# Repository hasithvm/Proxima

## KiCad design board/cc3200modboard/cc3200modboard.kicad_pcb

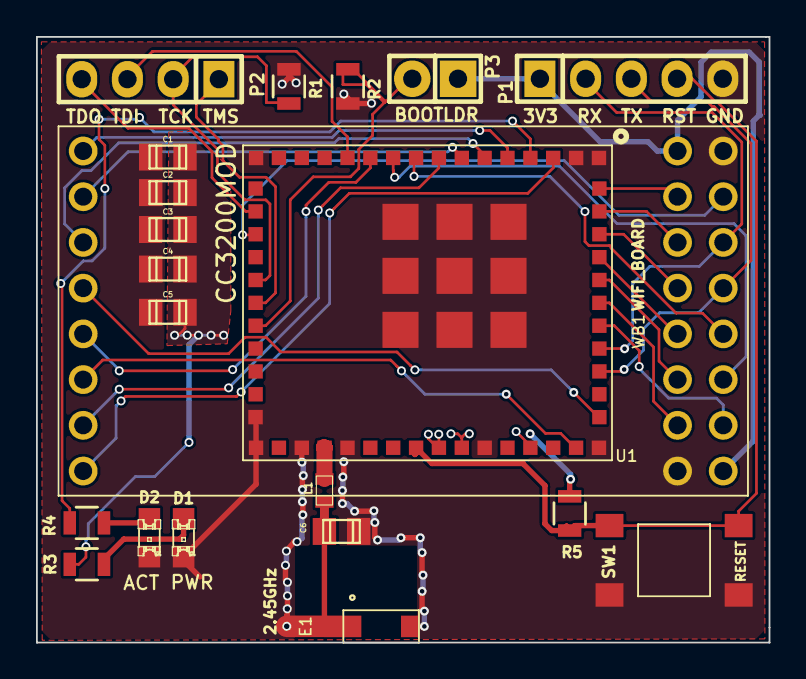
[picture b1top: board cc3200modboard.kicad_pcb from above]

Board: 2 copper layers, 40.7 x 33.6 mm, 21 parts (0 on the bottom side), 33 nets.

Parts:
C1, C2, C3, C4, C5: 22uF; c_0805
C6: 1.0pF; c_0805
D1: PWR; LED-0805
D2: ACT; LED-0805
E1: 2.45GHz; 2.4GHz_ANT_AH316M245001-T
L1: 3.6nH; IND_RF_0603
P1: PROG; Pin_Header_Straight_1x05
P2: JTAG; Pin_Header_Straight_1x04
P3: BOOTLDR; Pin_Header_Straight_1x02
R1: 100K; R_0805
R2: 2.7K; R_0805
R3, R4: 560; R_0805
R5: 10K; R_0805
SW1: RESET; PTS645
U1: CC3200MOD
WB1: WIFI_BOARD; DaughterBoard

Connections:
3V3: C1.1, C2.1, C3.1, C4.1, C5.1, P1.1, P3.1, R3.1, R5.1, U1.36, U1.37, U1.40, WB1.9, WB1.17
/GPIO0: U1.44, WB1.4
/GPIO1: P1.3, U1.46, WB1.13
/GPIO2: P1.2, U1.47, WB1.14
/GPIO3: U1.48, WB1.10
/GPIO4: U1.49, WB1.23
/GPIO5: U1.50, WB1.22
/GPIO6: U1.51, WB1.21
/GPIO7: U1.52, WB1.20
/GPIO8: U1.53, WB1.19
/GPIO9: U1.54, WB1.18
/GPIO10: U1.3, WB1.8
/GPIO11: R4.1, U1.4
/GPIO12: U1.9, WB1.12
/GPIO13: U1.10, WB1.11
/GPIO14: U1.5, WB1.1
/GPIO15: U1.6, WB1.3
/GPIO16: U1.7, WB1.2
/GPIO17: U1.8, WB1.7
/GPIO22: U1.11, WB1.5
/GPIO28: U1.19, WB1.15
/GPIO30: U1.42, WB1.6
/IMP_50OHM: L1.1, U1.31
/RF_FEED: C6.1, E1.1, L1.2
/SOP2: P3.2, R2.1, U1.23
/TCK: P2.2, R1.1, U1.21
/TDI: P2.3, U1.12
/TDO: P2.4, U1.18
/TMS: P2.1, U1.22
/nRESET: P1.4, R5.2, SW1.2, U1.35
GND: C1.2, C2.2, C3.2, C4.2, C5.2, C6.2, D1.2, D2.2, E1.2, P1.5, R1.2, R2.2, SW1.1, U1.1, U1.2, U1.16, U1.27, U1.28, U1.30, U1.32, U1.38, U1.43, U1.55, U1.56, U1.57, U1.58, U1.59, U1.60, U1.61, U1.62, U1.63, WB1.16, WB1.24
unnamed: D1.1, R3.2
unnamed: D2.1, R4.2

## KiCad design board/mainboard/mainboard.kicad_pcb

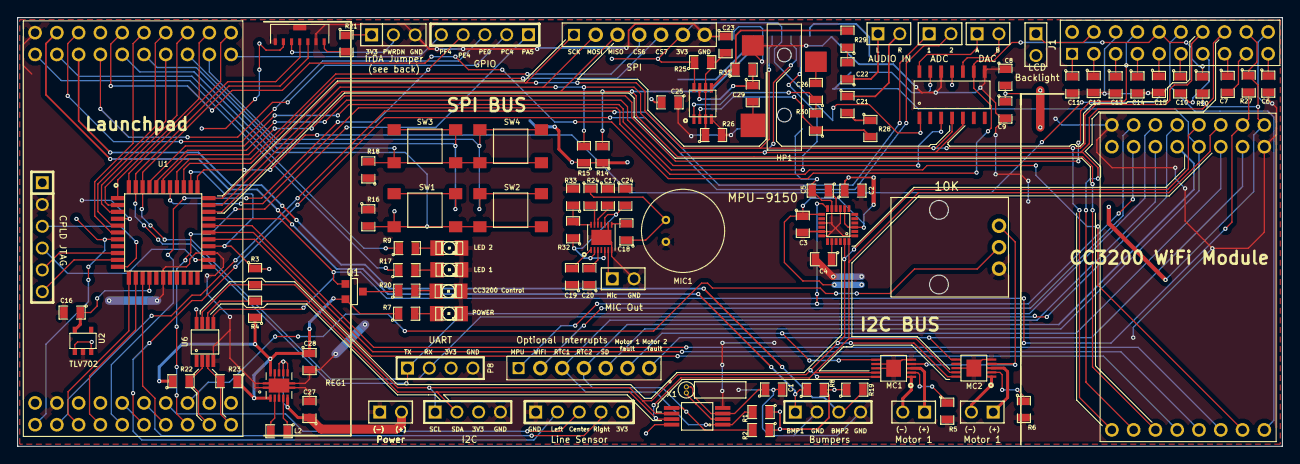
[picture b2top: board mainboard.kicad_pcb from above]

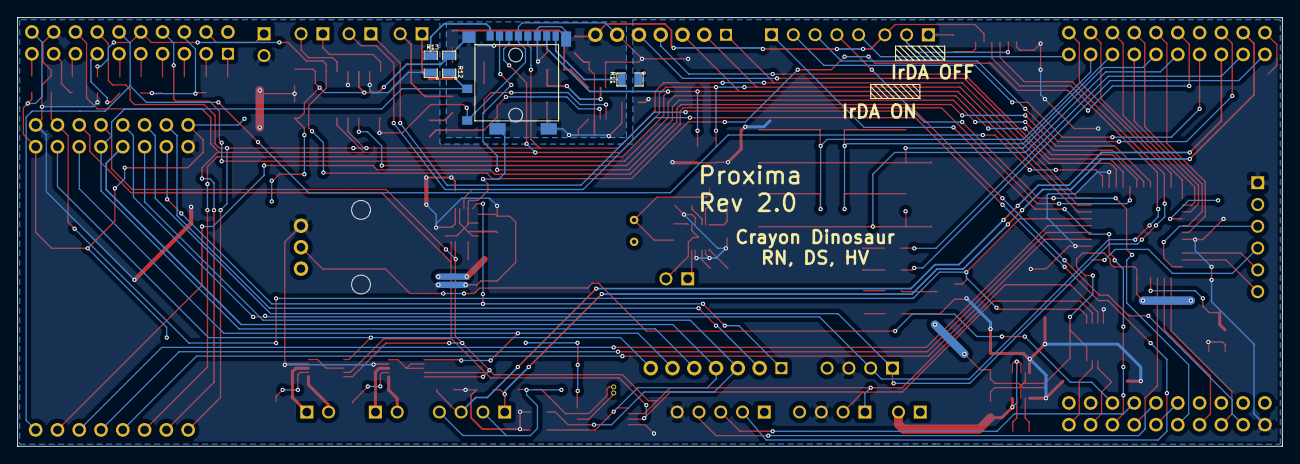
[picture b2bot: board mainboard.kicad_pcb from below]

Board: 2 copper layers, 147.5 x 50.0 mm, 109 parts (4 on the bottom side), 117 nets.

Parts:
AUD1: LM4808
C1: 5pF; SM0805
C2, C5, C8, C24: 0.1uF; SM0805
C3: 10nF; SM0805
C4: 2.2nF; SM0805
C6, C7, C10, C11, C12, C13, C14, C15, C16, C25: 1uF; SM0805
C9, C27, C28: 10uF; SM0805
C17: 470nF; SM0805
C18, C19: 680nF; SM0805
C20, C21, C22: 2.2uF; SM0805
C23: 1.0uF; SM0805
C26, C29: 100uF; SM0805
D1: GLED; LED-1206
D2: RLED; LED-1206
D3: POWER; LED-1206
D4: CONTROL; LED-1206
DAC1: MCP4902
GLCD1: NHD-C12832A1Z-NSW-BBW-3V3; 2x10_Headers
HP1: HP_JACK; HeadphoneJack
IR1: RPM841-H11; RPM973-H11
J1: BACKL; PIN_ARRAY_2X1
K1: IRDA_EN; PIN_ARRAY_3X1
L2: 2.2uH; SM0805
LP1: TIVALAUNCHPAD; TivaC
MC1, MC2: DRV8830; DRV8830MSOP
MIC1: CMA-4544PF-W; CMA-4544
MPU1: MPU-9150; MPU9150
P1: I2C; PIN_ARRAY_4x1
P2: Motor1; PIN_ARRAY_2X1
P3: Motor2; PIN_ARRAY_2X1
P4: SPI; 1x7_Headers
P5: DAC; PIN_ARRAY_2X1
P6: CONN_5; PIN_ARRAY_5x1
P7: ANALOG; PIN_ARRAY_2X1
P8: OPTIONAL_PERIPH; 1x7_Headers
P9: GPIO; PIN_ARRAY_5x1
P10: BUMPERS; PIN_ARRAY_4x1
P11: CPLD_JTAG; PIN_ARRAY-6X1
P12: POWER; PIN_ARRAY_2X1
P13: UART; PIN_ARRAY_4x1
P14: AUDIO; PIN_ARRAY_2X1
P15: MIC; PIN_ARRAY_2X1
Q1: BSS84; SOT23GDS
R1, R2, R16, R18, R27: 10K; SM0805
R3, R4, R22, R23: 4.7k; SM0805
R5, R6: 0.2; SM0805
R7, R9, R17, R20: 220; SM0805
R8, R11, R13, R14, R15, R19: 47k; SM0805
R10, R12: 10k; SM0805
R21: 3; SM0805
R24: 2.2k; SM0805
R25, R26: 100k; SM0805
R28, R29, R30, R31: 3.9k; SM0805
R32, R33: 150k; SM0805
REG1: TPS63001
RTC1: S-35390A; S35390A
RV1: 10K; P090_Potentiometer
SD1: SDCARD_PUSH; SDCARD_Push
SW1, SW2, SW3, SW4: SW_PUSH; PTS645
U1: XC2C32A; CoolrunnerII
U2: TLV702; SOT23-5
U3: MAX9814
U6: PCA9515B
WB1: WIFI_BOARD; DaughterBoard
X1: 32.768KHz; XTAL-32K

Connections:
3V3: AUD1.8, C2.1, C3.1, C8.2, C9.1, C24.2, C25.2, C28.1, DAC1.1, DAC1.11, DAC1.13, GLCD1.12, IR1.6, J1.2, K1.1, LP1.1, MC1.4, MC2.4, MPU1.3, MPU1.8, MPU1.13, P1.3, P4.6, P6.5, P11.1, P13.3, Q1.S, R1.1, R2.1, R3.1, R4.1, R7.1, R8.2, R10.2, R11.1, R13.1, R14.1, R15.1, R19.1, R21.1, R22.1, R23.1, R25.1, R27.1, R32.1, REG1.1, REG1.10, RTC1.8, RV1.3, SD1.4, SD1.9, U1.7, U1.26, U1.35, U2.1, U2.3, U3.2, U3.5, U3.10, U6.8, WB1.9, WB1.17
+1.8V: C16.1, U1.15, U2.5
AIN1: LP1.2, P7.1
AIN2: LP1.6, P7.2
BUMP1: LP1.19, P10.1, R8.1
BUMP2: LP1.38, P10.3, R19.2
CC_CONTROL: Q1.G, R27.2, U1.30, U6.5, WB1.10
CPLD_TCK: P11.3, U1.11
CPLD_TDI: P11.5, U1.9
CPLD_TDO: P11.4, U1.24
CPLD_TMS: P11.6, U1.10
GLCD_A0: GLCD1.15, U1.34, WB1.8
GLCD_A0_LP: LP1.34, U1.3
GND: AUD1.4, C1.2, C2.2, C3.2, C4.2, C5.2, C6.2, C8.1, C9.2, C11.2, C12.2, C13.2, C14.2, C15.2, C16.2, C17.1, C19.1, C20.1, C23.1, C24.1, C25.1, C27.2, C28.2, D1.2, D2.2, D3.2, D4.2, DAC1.8, DAC1.12, GLCD1.11, GLCD1.18, HP1.5, IR1.2, IR1.7, K1.3, LP1.20, LP1.22, MC1.5, MC1.7, MC1.8, MC2.5, MC2.8, MIC1.2, MPU1.1, MPU1.9, MPU1.11, MPU1.15, MPU1.17, MPU1.18, P1.4, P4.7, P6.1, P10.2, P10.4, P11.2, P12.1, P13.4, P15.2, R5.2, R6.2, R12.2, R16.1, R18.1, R26.2, R33.2, REG1.3, REG1.9, RTC1.4, RV1.1, SD1.6, U1.4, U1.17, U1.25, U2.2, U3.7, U3.9, U6.4, WB1.16, WB1.24
I2C_CL: MC1.10, MC2.10, MPU1.23, P1.1, R3.2, RTC1.6, U6.7, WB1.12
I2C_CL_LP: LP1.9, R22.2, U6.2
I2C_DA: MC1.9, MC2.9, MPU1.24, P1.2, R4.2, RTC1.7, U6.6, WB1.11
I2C_DA_LP: LP1.10, R23.2, U6.3
KPAD_C1: LP1.36, R16.2, SW1.2, SW2.2
KPAD_C2: LP1.35, R18.2, SW3.2, SW4.2
KPAD_R1: LP1.33, SW1.1, SW3.1
KPAD_R2: LP1.32, SW2.1, SW4.1
LED1: LP1.40, R17.1
LED2: LP1.39, R9.1
LINE_SENSOR_C: LP1.27, P6.3
LINE_SENSOR_L: LP1.25, P6.2
LINE_SENSOR_R: LP1.26, P6.4
MOTOR1+: MC1.3, P2.1
MOTOR1-: MC1.1, P2.2
MOTOR1F: MC1.6, P8.6, WB1.22
MOTOR2+: MC2.3, P3.1
MOTOR2-: MC2.1, P3.2
MOTOR2F: MC2.6, P8.7, WB1.23
MPUINT: MPU1.12, P8.1, WB1.18
unnamed: MC2.2, R6.1
unnamed: C5.1, MPU1.10
unnamed: C4.1, MPU1.20
unnamed: MC1.2, R5.1
unnamed: C1.1, RTC1.3, X1.1
unnamed: RTC1.2, X1.2
unnamed: DAC1.10, P5.2
unnamed: DAC1.14, P5.1
unnamed: R13.2, SD1.1
unnamed: C15.1, GLCD1.5
unnamed: C14.1, GLCD1.4
unnamed: C13.1, GLCD1.3
unnamed: C12.1, GLCD1.2
unnamed: C6.1, GLCD1.10
unnamed: C11.1, GLCD1.1
unnamed: R11.2, SD1.8
unnamed: GLCD1.19, J1.1
unnamed: C10.1, GLCD1.6
unnamed: C7.1, GLCD1.8
unnamed: C7.2, GLCD1.9
unnamed: C10.2, GLCD1.7
unnamed: D2.1, R17.2
unnamed: IR1.5, K1.2
unnamed: IR1.1, R21.2
unnamed: Q1.D, R20.1
unnamed: D3.1, R7.2
unnamed: D1.1, R9.2
unnamed: D4.1, R20.2
unnamed: L2.2, REG1.2
unnamed: L2.1, REG1.4
unnamed: C27.1, P12.2, REG1.5, REG1.6, REG1.7, REG1.8
unnamed: AUD1.7, C29.1, R31.2
unnamed: C22.2, R29.1
unnamed: AUD1.3, AUD1.6, C23.2, R25.2, R26.1
unnamed: AUD1.5, R29.2, R31.1
unnamed: AUD1.2, R28.2, R30.1
unnamed: C29.2, HP1.4
unnamed: C26.2, HP1.1
unnamed: C22.1, P14.1
unnamed: C21.1, P14.2
unnamed: C17.2, U3.12
unnamed: R32.2, R33.1, U3.14
unnamed: P15.1, U3.6
unnamed: AUD1.1, C26.1, R30.2
unnamed: C21.2, R28.1
unnamed: C20.2, U3.3
unnamed: R24.2, U3.13
unnamed: C18.1, MIC1.1, R24.1
unnamed: C18.2, U3.8
unnamed: C19.2, U3.1
PA5: LP1.8, P9.1
PC4: LP1.37, P9.2
PE0: LP1.18, P9.3
PE4: LP1.5, P9.4
PF4: LP1.31, P9.5
POT: LP1.28, RV1.2
RST: DAC1.9, GLCD1.16, LP1.16, R10.1
RTCINT1: P8.3, R1.2, RTC1.1, WB1.19
RTCINT2: P8.4, R2.2, RTC1.5, WB1.20
SD_SWITCH: P8.5, R12.1, SD1.10, WB1.21
SPI_CS1: SD1.2, U1.41
SPI_CS2: DAC1.3, U1.40
SPI_CS3: GLCD1.17, U1.39
SPI_CS5: U1.38, WB1.7
SPI_CS6: P4.4, U1.37
SPI_CS7: P4.5, U1.36
SPI_MISO: P4.3, R14.2, SD1.7, U1.31, WB1.3
SPI_MISO_LP: LP1.14, U1.5
SPI_MOSI: DAC1.5, GLCD1.13, P4.2, R15.2, SD1.3, U1.32, WB1.2
SPI_MOSI_LP: LP1.15, U1.6
SPI_SCK: DAC1.4, GLCD1.14, P4.1, SD1.5, U1.33, WB1.1
SPI_SCK_LP: LP1.7, U1.14
SPI_SEL0_CC: U1.27, WB1.4
SPI_SEL0_LP: LP1.11, U1.44
SPI_SEL1_CC: U1.28, WB1.5
SPI_SEL1_LP: LP1.12, U1.1
SPI_SEL2_CC: U1.29, WB1.6
SPI_SEL2_LP: LP1.13, U1.2
UART_RX: IR1.3, P13.2, U1.42, WB1.13
UART_RX_LP: LP1.3, U1.12
UART_TX: IR1.4, P13.1, U1.43, WB1.14
UART_TX_LP: LP1.4, U1.13
WIFI_INT: P8.2, WB1.15

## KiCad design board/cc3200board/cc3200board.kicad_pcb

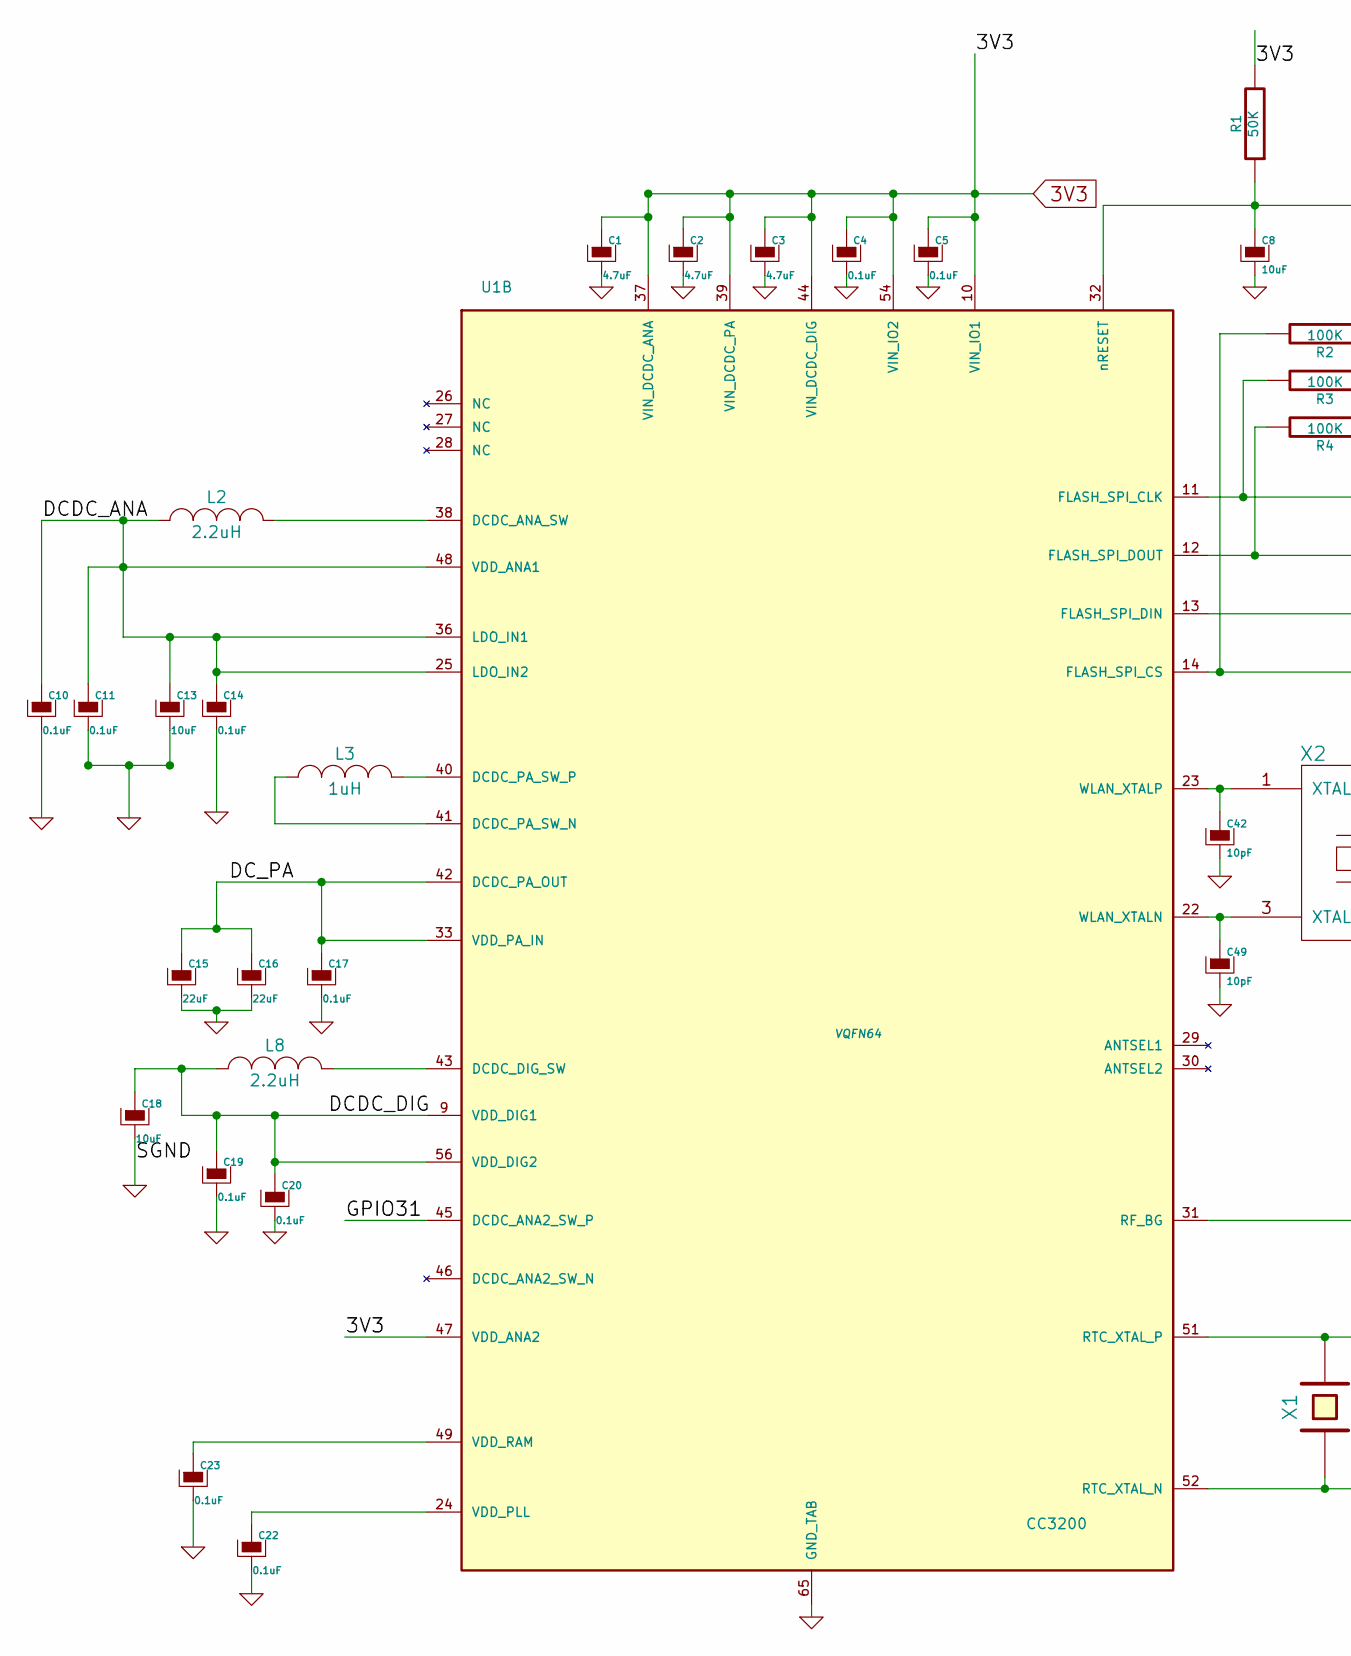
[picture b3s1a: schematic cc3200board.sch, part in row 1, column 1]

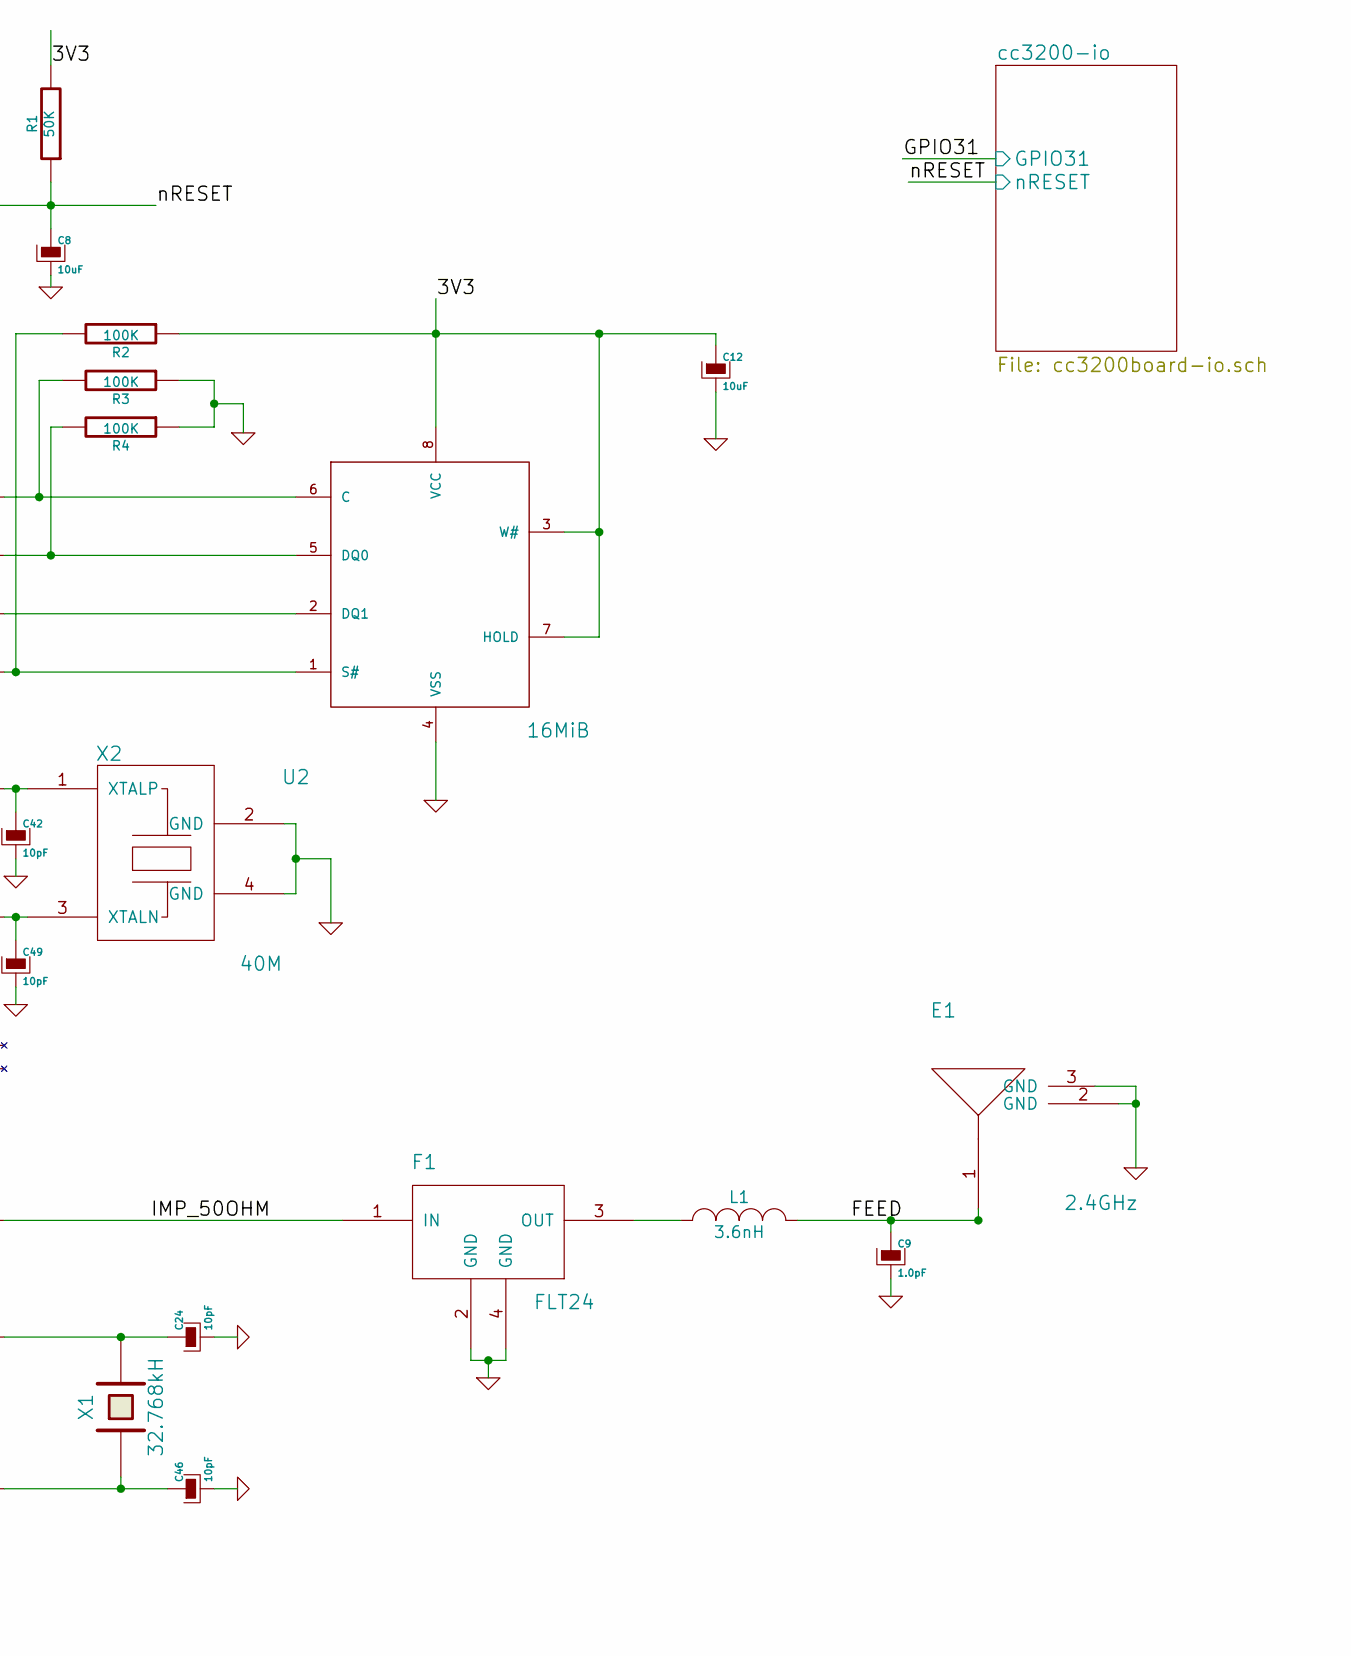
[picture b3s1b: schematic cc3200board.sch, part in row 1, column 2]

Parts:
C1, C2, C3: 4.7uF
C4, C5, C10, C11, C14, C17, C19, C20, C22, C23: 0.1uF
C8, C12, C13, C18: 10uF
C9: 1.0pF
C15, C16: 22uF
C24, C42, C46, C49: 10pF
E1: 2.4GHz; PartNum AH316M245001-T
F1: FLT24
L1: 3.6nH
L2, L8: 2.2uH
L3: 1uH
R1: 50K
R2, R3, R4: 100K
U1: CC3200; VQFN64; PartNum CC3200R1M2RGCR
U2: 16MiB; PartNum N25Q128A13ESE40E
X1: 32.768kH
X2: 40M; PartNumber ABM3B-40.000MHZ-10-1-U-T

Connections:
3V3: C1.1, C2.1, C3.1, C4.1, C5.1, C12.1, R1.2, R2.1, U1.10 (VIN_IO1), U1.37 (VIN_DCDC_ANA), U1.39 (VIN_DCDC_PA), U1.44 (VIN_DCDC_DIG), U1.47 (VDD_ANA2), U1.54 (VIN_IO2), U2.3 (W#), U2.7 (HOLD), U2.8 (VCC); also elsewhere on the board
/DCDC_ANA: C10.1, C11.1, C13.1, C14.1, L2.1, U1.25 (LDO_IN2), U1.36 (LDO_IN1), U1.48 (VDD_ANA1)
/DCDC_DIG: C18.1, C19.1, C20.1, L8.1, U1.9 (VDD_DIG1), U1.56 (VDD_DIG2)
/DC_PA: C15.1, C16.1, C17.1, U1.33 (VDD_PA_IN), U1.42 (DCDC_PA_OUT)
/FEED: C9.1, E1.1, L1.2
/IMP_50OHM: F1.1 (IN), U1.31 (RF_BG)
/cc3200-io/GPIO31: U1.45 (DCDC_ANA2_SW_P); also elsewhere on the board
/cc3200-io/nRESET: C8.1, R1.1, U1.32 (nRESET); also elsewhere on the board
GND: C1.2, C2.2, C3.2, C4.2, C5.2, C8.2, C9.2, C10.2, C11.2, C12.2, C13.2, C14.2, C15.2, C16.2, C17.2, C18.2, C19.2, C20.2, C22.2, C23.2, C24.2, C42.2, C46.2, C49.2, E1.2 (GND), E1.3 (GND), F1.2 (GND), F1.4 (GND), R3.1, R4.1, U1.65 (GND_TAB), U2.4 (VSS), X2.2 (GND), X2.4 (GND); also elsewhere on the board
unnamed: C22.1, U1.24 (VDD_PLL)
unnamed: C23.1, U1.49 (VDD_RAM)
unnamed: C24.1, U1.51 (RTC_XTAL_P), X1.2
unnamed: C42.1, U1.23 (WLAN_XTALP), X2.1 (XTALP)
unnamed: C46.1, U1.52 (RTC_XTAL_N), X1.1
unnamed: C49.1, U1.22 (WLAN_XTALN), X2.3 (XTALN)
unnamed: F1.3 (OUT), L1.1
unnamed: L2.2, U1.38 (DCDC_ANA_SW)
unnamed: L3.1, U1.41 (DCDC_PA_SW_N)
unnamed: L3.2, U1.40 (DCDC_PA_SW_P)
unnamed: L8.2, U1.43 (DCDC_DIG_SW)
unnamed: R2.2, U1.14 (FLASH_SPI_CS), U2.1 (S#)
unnamed: R3.2, U1.11 (FLASH_SPI_CLK), U2.6 (C)
unnamed: R4.2, U1.12 (FLASH_SPI_DOUT), U2.5 (DQ0)
unnamed: U1.13 (FLASH_SPI_DIN), U2.2 (DQ1)

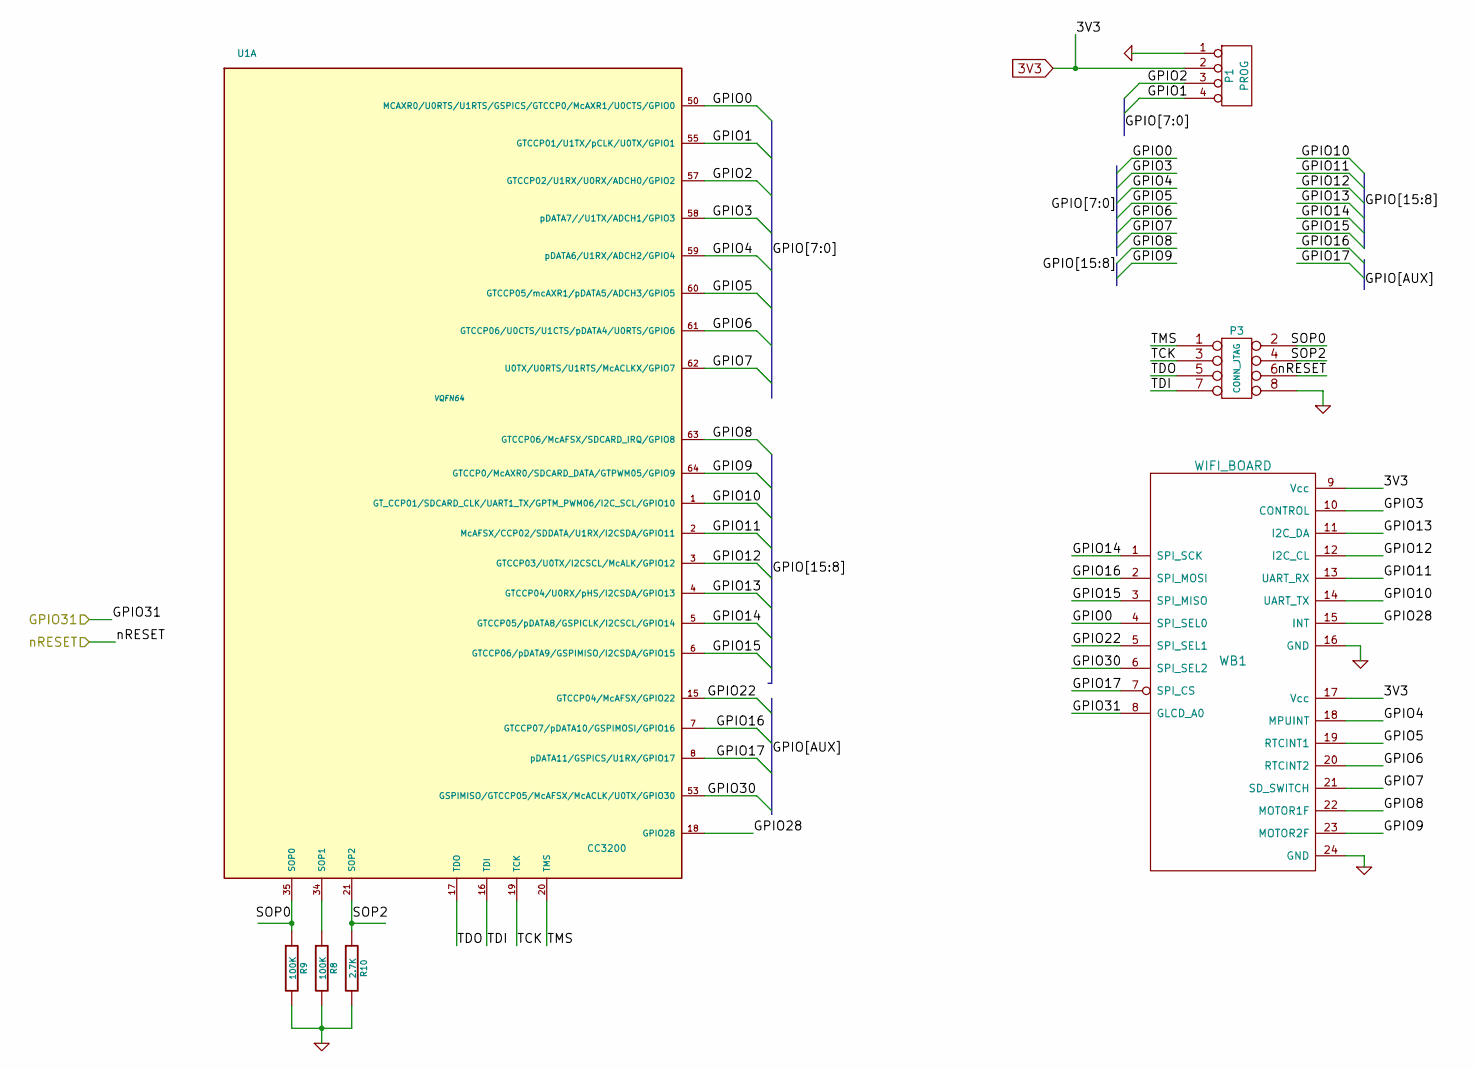
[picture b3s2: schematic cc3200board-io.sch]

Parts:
P1: PROG
P3: CONN_JTAG
R8, R9: 100K
R10: 2.7K
U1: CC3200; VQFN64
WB1: WIFI_BOARD

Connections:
3V3: P1.2, WB1.9 (Vcc), WB1.17 (Vcc); also elsewhere on the board
/cc3200-io/GPIO0: U1.50 (MCAXR0/U0RTS/U1RTS/GSPICS/GTCCP0/McAXR1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), WB1.4 (SPI_SEL0)
/cc3200-io/GPIO1: P1.4, U1.55 (GTCCP01/U1TX/pCLK/U0TX/GPIO1)
/cc3200-io/GPIO2: P1.3, U1.57 (GTCCP02/U1RX/U0RX/ADCH0/GPIO2)
/cc3200-io/GPIO3: U1.58 (pDATA7//U1TX/ADCH1/GPIO3), WB1.10 (CONTROL)
/cc3200-io/GPIO4: U1.59 (pDATA6/U1RX/ADCH2/GPIO4), WB1.18 (MPUINT)
/cc3200-io/GPIO5: U1.60 (GTCCP05/mcAXR1/pDATA5/ADCH3/GPIO5), WB1.19 (RTCINT1)
/cc3200-io/GPIO6: U1.61 (GTCCP06/U0CTS/U1CTS/pDATA4/U0RTS/GPIO6), WB1.20 (RTCINT2)
/cc3200-io/GPIO7: U1.62 (U0TX/U0RTS/U1RTS/McACLKX/GPIO7), WB1.21 (SD_SWITCH)
/cc3200-io/GPIO8: U1.63 (GTCCP06/McAFSX/SDCARD_IRQ/GPIO8), WB1.22 (MOTOR1F)
/cc3200-io/GPIO9: U1.64 (GTCCP0/McAXR0/SDCARD_DATA/GTPWM05/GPIO9), WB1.23 (MOTOR2F)
/cc3200-io/GPIO10: U1.1 (GT_CCP01/SDCARD_CLK/UART1_TX/GPTM_PWM06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), WB1.14 (UART_TX)
/cc3200-io/GPIO11: U1.2 (McAFSX/CCP02/SDDATA/U1RX/I2CSDA/GPIO11), WB1.13 (UART_RX)
/cc3200-io/GPIO12: U1.3 (GTCCP03/U0TX/I2CSCL/McALK/GPIO12), WB1.12 (I2C_CL)
/cc3200-io/GPIO13: U1.4 (GTCCP04/U0RX/pHS/I2CSDA/GPIO13), WB1.11 (I2C_DA)
/cc3200-io/GPIO14: U1.5 (GTCCP05/pDATA8/GSPICLK/I2CSCL/GPIO14), WB1.1 (SPI_SCK)
/cc3200-io/GPIO15: U1.6 (GTCCP06/pDATA9/GSPIMISO/I2CSDA/GPIO15), WB1.3 (SPI_MISO)
/cc3200-io/GPIO16: U1.7 (GTCCP07/pDATA10/GSPIMOSI/GPIO16), WB1.2 (SPI_MOSI)
/cc3200-io/GPIO17: U1.8 (pDATA11/GSPICS/U1RX/GPIO17), WB1.7 (SPI_CS)
/cc3200-io/GPIO22: U1.15 (GTCCP04/McAFSX/GPIO22), WB1.5 (SPI_SEL1)
/cc3200-io/GPIO28: U1.18 (GPIO28), WB1.15 (INT)
/cc3200-io/GPIO30: U1.53 (GSPIMISO/GTCCP05/McAFSX/McACLK/U0TX/GPI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), WB1.6 (SPI_SEL2)
/cc3200-io/GPIO31: WB1.8 (GLCD_A0); also elsewhere on the board
/cc3200-io/SOP0: P3.2, R9.1, U1.35 (SOP0)
/cc3200-io/SOP2: P3.4, R10.1, U1.21 (SOP2)
/cc3200-io/TCK: P3.3, U1.19 (TCK)
/cc3200-io/TDI: P3.7, U1.16 (TDI)
/cc3200-io/TDO: P3.5, U1.17 (TDO)
/cc3200-io/TMS: P3.1, U1.20 (TMS)
/cc3200-io/nRESET: P3.6; also elsewhere on the board
GND: P1.1, P3.8, R8.2, R9.2, R10.2, WB1.16 (GND), WB1.24 (GND); also elsewhere on the board
unnamed: R8.1, U1.34 (SOP1)

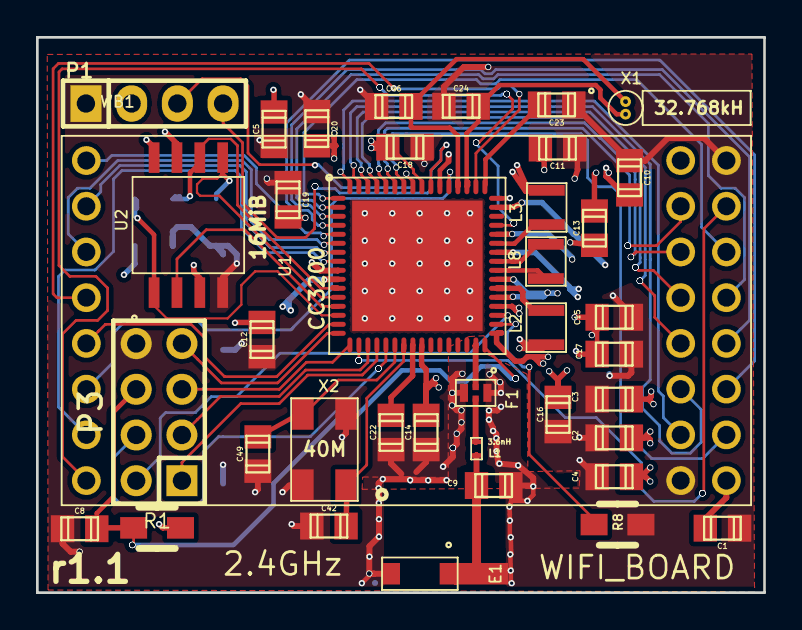
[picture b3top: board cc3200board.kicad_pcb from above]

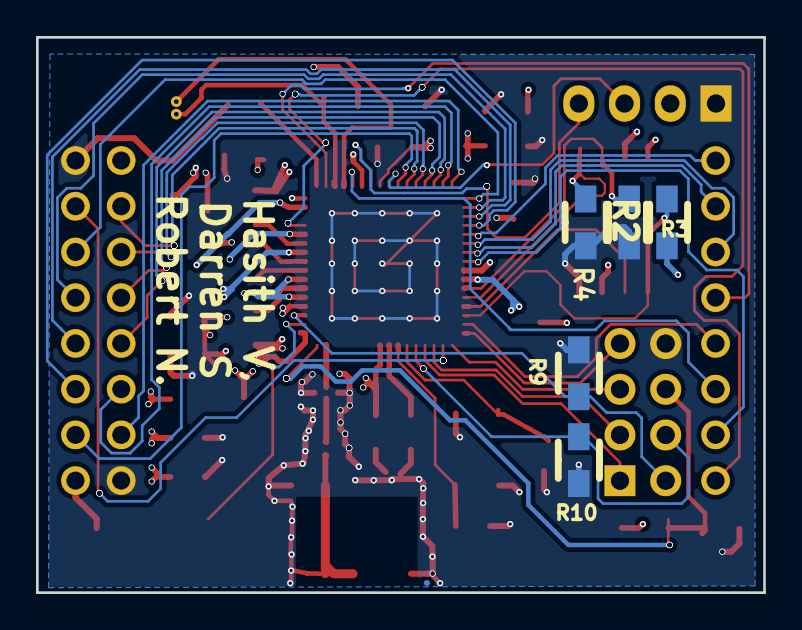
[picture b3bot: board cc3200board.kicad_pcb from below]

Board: 4 copper layers, 40.4 x 30.8 mm, 44 parts (5 on the bottom side), 52 nets.

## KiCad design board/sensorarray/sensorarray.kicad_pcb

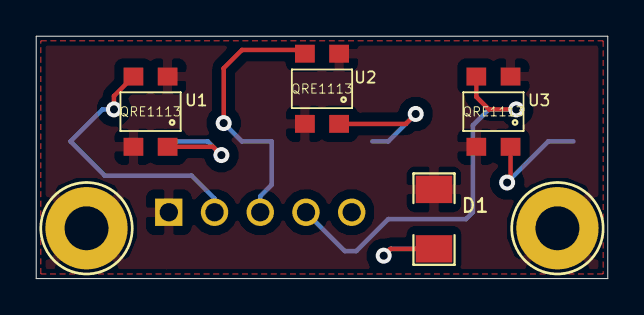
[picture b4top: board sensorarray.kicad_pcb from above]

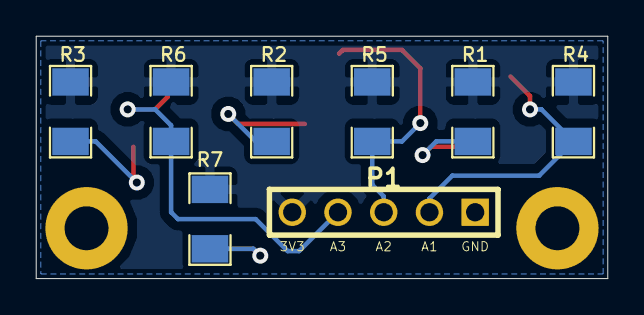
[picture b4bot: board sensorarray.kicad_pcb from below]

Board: 2 copper layers, 31.8 x 13.5 mm, 14 parts (8 on the bottom side), 9 nets.

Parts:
D1: DIODE; SM1206
P1: CONN_5; PIN_ARRAY_5x1
P2, P3: CONN_1; 2-48_mount
R1, R2, R3: 56; SM1206
R4, R5, R6: 8.2k; SM1206
R7: 10k; SM1206
U1, U2, U3: QRE1113

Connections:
3V3: P1.5, R1.1, R2.1, R3.1, R4.1, R5.1, R6.1, R7.1
A1: P1.2, R4.2, U1.3
A2: P1.3, R5.2, U2.3
A3: P1.4, R6.2, U3.3
GND: D1.1, P1.1, P2.1, P3.1, U1.2, U1.4, U2.2, U2.4, U3.2, U3.4
unnamed: R3.2, U3.1
unnamed: D1.2, R7.2
unnamed: R2.2, U2.1
unnamed: R1.2, U1.1

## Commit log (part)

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2014-09-28 Added first meeting minutes and peripheral list
2014-09-28 Added first submission of proposal
2014-09-28 Add initial version of the CC3200 bootloader
2014-09-28 Added bootloader interface scripts
2014-09-28 Added CC3200 udev scripts
2014-09-28 Ignore bootloader binaries
2014-09-28 Fixed default CC3200 SDK installation location
2014-09-28 Move bootloader into cc3200 folder
2014-09-29 Reduced stack size
2014-09-29 Fixed argument parsing for 2 args
2014-09-29 Bootloader checks for sw2 push on startup
2014-09-29 OFLAGS will disable debug and insert optimizations
2014-09-29 Added gdb init script and openocd config script
2014-09-30 Bootloader now bootloads /usr/appimg.bin
2014-09-30 Bootloader can now quit without reset
2014-09-30 Cleaned up scripts and added quit script
2014-09-30 Added schematic for MPU9150 device
2014-10-04 Updated proposal with final copy
2014-10-04 Updated peripheral list with some suppliers and prices
2014-10-07 Added block diagram
2014-10-20 Added MPU9150 footprint
2014-10-20 Increased land width for MPU9150
2014-10-20 Changed id of RTC to include package type
2014-10-20 Added TMP100 footprint
2014-10-20 Added DRV8830 footprint
2014-10-20 Added datasheets for the MPU and DRV chips
2014-10-20 Added temp sensor datasheet
2014-10-20 Added sdcard datasheet
2014-10-20 Added SD card footprint
2014-10-20 Added audio codec datasheet
2014-10-20 Renamed SDCard to indicate type
2014-10-20 Added audio codec footprint
2014-10-20 Added pin 1 market to audio codec
2014-10-20 Added dac datasheet
2014-10-20 Added dac footprint
2014-10-21 Added the LCD footprint
2014-10-21 Added mainboard KiCad files, DRV8830, MPU-9150, and TMP100
2014-10-21 Added WM8731 part to library
2014-10-21 Added TLV5626 part to library
2014-10-21 Added push sdcard footprint
2014-10-21 Added SDCARD parts to library
2014-10-21 Added push sdcard socket datasheet
2014-10-21 Committing in-progress work on redoing the CC3200 symbol
2014-10-22 Added launchpad footprint
2014-10-22 Added rtc datasheet
2014-10-22 Added TivaLaunchpad part
2014-10-22 Added peripherals schematic with TMP100 reference design
2014-10-22 Added cache libraries to gitignore
2014-10-22 Exported MadParts to KiCad library
2014-10-23 Added KiCad autosaves to gitignore
2014-10-23 Added RTC to parts library
2014-10-23 Added vim files to gitignore
2014-10-23 Added schematic for RTC
2014-10-23 Added The motor driver circuits
2014-10-23 Fixed motor controller 2 connecting to motor 1 nets
2014-10-23 Removed unnecessary no-connects
2014-10-23 Renamed peripherals schematic to i2c_peripherals
2014-10-23 Added MPU schematic
2014-10-23 Fixed reference to i2c peripherals in mainboard
2014-10-23 Added SPI peripherals and SD Card schematic
2014-10-23 Added datasheet for SPI flash part
2014-10-31 Finalized power/RF subsystems for CC3200board
2014-10-31 Added initial GPIO/JTAG/SOP breakout pins. Impedance controlled traces labelled.
2014-10-31 Fixed VQFN64 footprint
2014-11-01 Added schematic for DAC
2014-11-02 Added footprints for all CC3200 components
2014-11-02 Added datasheets for the new DAC, the GLCD, and the inverter
2014-11-02 Added MCP footprint
2014-11-11 Changed pull-down on SD card to 10k
2014-11-11 Fixed which RST feeds the inverter, might be able to remove it
2014-11-11 Changed RSVD pins on Tiva to DNC
2014-11-11 Added NHD GLCD part to library
2014-11-11 Added GLCD to schematic
2014-11-11 Removed RST inverter
2014-11-15 Swapped DAC to one in mainboard library
2014-11-15 Removed old DAC from datasheets
2014-11-16 Added sensor array, with schematic, datasheet, and QRE11131GR part
2014-11-17 Removed temperature sensor
2014-11-17 Added Audio codec and launchpad connection schematics
2014-11-17 Updated peripheral listing document
2014-11-17 Added footprint for QRE1113
2014-11-18 Added simple peripherals to launchpad schematic
2014-11-18 Added SPI CS decoder
2014-11-18 First version of the PCB layout of the sensor array
2014-11-18 Swapped the diode OR gate on the 3-8 to pulldowns
2014-11-18 Committing final changes
2014-11-18 Added missing no-connect flags to line-out on codec
2014-11-18 Added i2c exposed header
2014-11-18 Named some default named connectors, fixed incorrect pull down
2014-11-18 Added mounting holes, removed dimensions
2014-11-18 Fixed crystals and added mic to audio codec
2014-11-18 Added notation for mounting holes
2014-11-18 Added copper pour
2014-11-18 Added SilkS labels for pins
2014-11-18 Footprints update, planning update
2014-11-19 Added connector for Line Sensors, and fixed pots/photsensors
2014-11-23 Changed buffers to 3v3 compatible version
2014-11-23 Added CC3200 bus cutoff schematics
2014-11-23 Added I2C transceiver
2014-11-23 Added i2c transceiver datasheet
2014-11-23 Added i2c transciever footprint
2014-11-23 Added header containing all interrupt pins
2014-11-23 Doubled the power pins, and added interrupt out to bb interface
2014-11-23 Replaced cc3200 bus isolation with jumpers
2014-11-23 Added daughterboard footprint
2014-11-23 Added Board to Board part to mainboard.lib
2014-11-23 Fixed silk overlapping pads
2014-11-23 Fixed incorrect part description for I2C Transceiver
2014-11-23 Updated board-to-board interface definition with CC3200 GPIO lines
2014-11-23 Added connections to Wifi Board
2014-11-23 Added header for remaining GPIOs on Launchpad
2014-11-23 Fixed silk on pads in pcb layout
2014-11-23 Fixed CC3200 symbol, missing GPIO28 pin. Complete pin check on symbol
2014-11-23 Fixing SPI bugs, adding SPI port
2014-11-24 Cleaning up some SPI connections, nothing functional
2014-11-24 Added missing pullups on the RTC interrupt lines
2014-11-24 Split the motors into two separate headers
2014-11-24 Added a jumper to the backlight on the GLCD
2014-11-24 Added coupling capacitors to DAC
2014-11-24 Added decoupling caps to the codec
2014-11-24 Added reference schematic for codec
2014-11-24 Finished schematic layout
2014-11-24 added 50k pullup to CS1 again, since we can leave it unpopulated
2014-11-24 Added headphone jack for codec
2014-11-24 Added footprint for headphone jack
2014-11-24 Added net names, fixed misnamed GLCD_A0
2014-11-24 Fixed double use of SPI_CS4
2014-11-24 Added power converter datasheet
2014-11-24 Added power regulator
2014-11-24 Added power regulator footprint
2014-11-24 Fixed mirrored footprint, outlines
2014-11-24 Moved MPU silkscreen off of the pads
2014-11-24 Improved pad placement and labelling for PowerPad chips
2014-11-24 Increased silk spacing on PCA9515B
2014-11-24 Fixed SDCARD silkscreen overlapping pins
2014-11-24 fix merge conflict in footprints
2014-11-24 Fixed some silkscreen stuff
2014-11-24 Added net name for swapped header row
2014-11-24 Exported footprints
2014-11-24 Added footprint for 32.768KHz xtal
2014-11-24 Annotations, DRC fixing, and first round of footprint matching
2014-11-24 Added HC-49US footprint
2014-11-24 Exported crystal footprint
2014-11-25 Added some standard header footprints
2014-11-25 Added inductor footprints for the 1008 and 0402 packages
2014-11-25 Can't use quotes in madpart descriptions
2014-11-25 Added Mic footprint
2014-11-25 Fixed flipped pin direction on mic footprint
2014-11-25 Added pushbutton footprint
2014-11-25 Added pushbutton datasheet
2014-11-25 Made pin1 on headers square
2014-11-25 Increased hole and pad size for headers
2014-11-25 Added Audio coded net to optional peripherals header
2014-11-25 Exporting footprints
2014-11-25 Exported netlist and matched footprints
2014-11-25 Preliminary PCB layout, not much
2014-11-25 Added CAP footprint for 330uF
2014-11-25 Finished first draft of rev 1 board
2014-11-27 Rev1.1 layout, without passives
2014-11-28 Temporary reorg commit
2014-11-28 SPI and I2C busses nearly finished, Most traces in place, except for the longest ones
2014-11-28 Added footprint for IrDA module
2014-11-28 Added IrDA Datasheet
2014-11-29 All but Spi_CS and power are routed.
2014-11-29 Routed PA and DIG power planes
2014-11-29 Added Vishay IrDA module footprint
2014-11-29 Completed power reroute, PCB plane cleanup. Two DRC violations on DCDC_DIG and DCDC_ANA intersection left.
2014-11-30 All finished but the power and GND
2014-11-30 Finished major layout, RF vias and final ground pins left
2014-12-01 Rev 1.0 of CC3200board
2014-12-01 Fixed error in GND plane on L4
2014-12-01 Finished Rev1.1, everything is connected, but not double checked yet
2014-12-01 Removed traces from holes
2014-12-02 Final cleanups, ready for silk
2014-12-02 Changed thermal relief of the zones to solid
2014-12-02 Updated RTC footprint to move the pin 1 marker inside the part
2014-12-02 Added Silk for SPI and I2C bus
2014-12-02 removed dimensions from edge layer
2014-12-02 Fixed busses to be same width
2014-12-02 Fixed bug with an unconnected net
2014-12-02 Added Penguin Skywalker
2014-12-02 Added bin folder to gitignore, generating gerbers there
2014-12-02 Revision 1.1 commit. Version submitted to OSH
2015-01-25 Fixed layout issues with mainboard v1.1
    * Increased width of power traces
    * Increased number of traces connecting power and ground planes
    * Cleaned up some routing
    * Reduced via size
2015-01-26 Removed audio codec from layout.
2015-02-03 Initial commit for CPLD experimentation Working firmware for SPI passthrough
2015-02-12 Added footprint for CPLD
2015-02-13 Added CPLD part
2015-02-13 Replaced buffers with CPLD
2015-02-13 Added CPLD footprint to mod file
2015-02-13 Various fixes to schematics and footprints:
    * Added pullup resistors to bumpers
    * Changed value of RLED resistor
    * Added resistor to GLED
    * Changed SPI pullup resistors to 47k
    * Added JTAG header for CPLD
    * Changed motor driver footprint to MSOP
2015-02-17 Added power LED, removed Codec Peripheral pin
2015-02-26 Various changes
    * Began Rev2 Layout
    * Added Pullup Resistors to LP I2C
    * Added IrDA Module
2015-02-28 Added LM4808 audio output to headphones
2015-02-28 First revision of mic and MAX9814, not finished
2015-02-28 Added 1.8v regulator datasheet
2015-02-28 Further work on the rev2 layout
2015-03-01 Finished draft 1 of Rev 2 layout
2015-03-01 Started work on CC3200MOD board
2015-03-01 Finalized schematic for CC3200MOD board
    1. Added new power and activity LEDs.
    2. Moved UART from GPIO10/11 to GPIO1/2, freeing up two pins.
    3. GPIO31 no longer available.
2015-03-01 Modified specdoc for interface
2015-03-01 Modified to make markdown work
2015-03-01 Apparently I forgot to save the most recent changes
2015-03-02 Full rework of all the silk screen, including bus labels, header labels, chip labels
2015-03-02 Condensed IrDA silk, changed A/B to L/R for Audio in
2015-03-02 Fixed reversed IrDA module instructions
2015-03-02 fixed DRC errors on schematic
2015-03-02 Finalized routing for cc3200mod board
2015-03-02 Moved a trace farther from the edge
2015-03-03 Added gerber outputs for rev2
2015-03-03 Final version of rev 2
2015-03-05 Added 2x10 header to footprint file again
2015-03-06 Added lcd board
2015-03-09 Added mounting holes for lcdboard, and fab outputs
2015-03-09 Committed version of CC3200 PCB for r2
2015-03-09 Cleanup of project folder
2015-03-09 Merging in cc3200modboard
2015-03-12 CC3200MOD footprint fix
2015-03-15 Finished revision 2 of WiFi Board
2015-03-18 Fixed 1.8 regulator pin swap, fixed crystal drill sizes, added flows
2015-03-23 Initial revision of C libraries, uart and adc started
2015-03-24 Changed enum constant names to reflect being constants
2015-03-24 Added GPIO support initial version
2015-07-13 Rebuilt power section to support switching, new buck converter for 3V3 net.
2015-07-14 Added capacitive touch/slider components Removed potentiometer as component
2015-07-14 Changed analog header to expose 3 analog inputs (freed up from removing potentiometer)
2015-07-14 Fixes for mainboard 1) Fixed IrDA module footprint, and UART lines. 2) Replaced SPI footprint with header for external LCD
2015-07-16 Completed work on I2C motor driver unit. 1) Added new motor drivers + I2C controller 2) Added headers for SWD for the KE40 device
2015-07-17 Completed rev 3.0 schematics.
    1) Replaced MPU with STM Accelerometer
2015-07-19 Added SPI Flash chip
2015-07-19 Slimmed down SPI header, added pullups in right locations. Added pullup on SPI flash CS
2015-07-22 Added most of the footprints needed to make this work
